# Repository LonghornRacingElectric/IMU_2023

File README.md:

# IMU Board
### ver. 2023
The hardware board containing the inertial measurement unit (IMU)

## Purpose
This board logs 6-axis accelerometer and gyroscope data and sends that data across the attached CAN bus.

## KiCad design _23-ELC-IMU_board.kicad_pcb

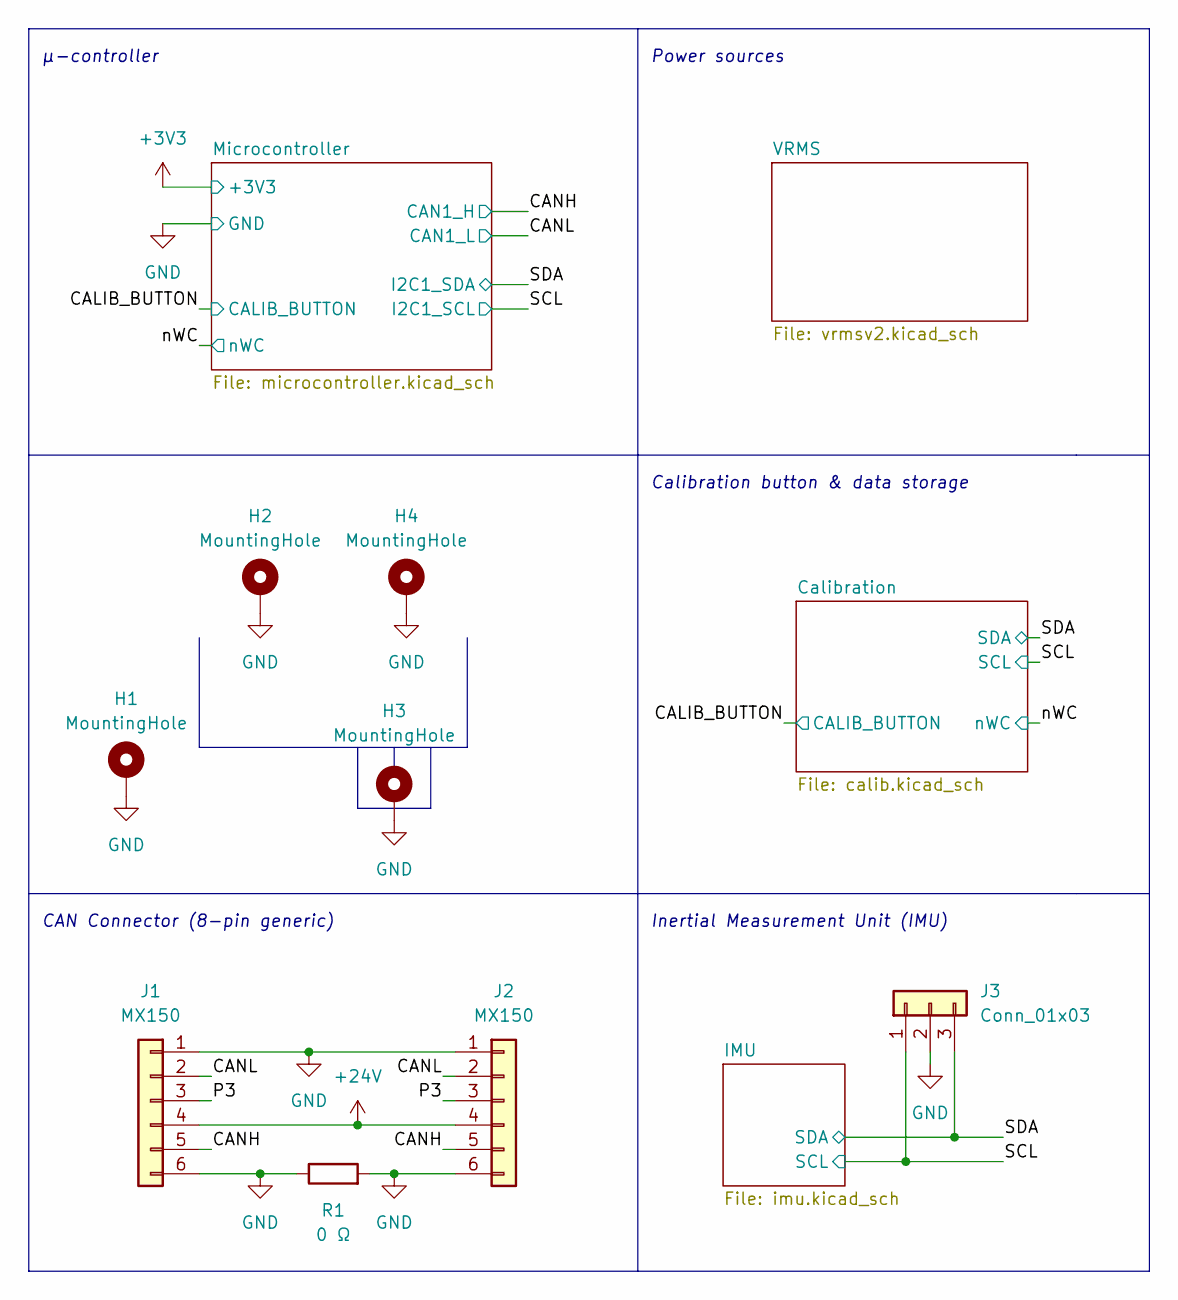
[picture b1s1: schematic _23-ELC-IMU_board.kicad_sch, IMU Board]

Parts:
H1, H2, H3, H4: MountingHole; MountingHole_3.5mm_Pad
J1, J2: MX150; Molex_Micro-Fit_3.0_43045-0600_2x03_P3.00mm_Horizontal
J3: Conn_01x03; PinHeader_1x03_P1.27mm_Vertical_SMD_Pin1Left
R1: 0 Ω; R_0603_1608Metric_Pad0.98x0.95mm_HandSolder

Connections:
+24V: J1.4, J2.4; also elsewhere on the board
/CANH: J1.5, J2.5; also elsewhere on the board
/CANL: J1.2, J2.2; also elsewhere on the board
/P3: J1.3, J2.3
/SCL: J3.1; also elsewhere on the board
/SDA: J3.3; also elsewhere on the board
GND: H1.1, H2.1, H3.1, H4.1, J1.1, J1.6, J2.1, J2.6, J3.2, R1.1, R1.2; also elsewhere on the board

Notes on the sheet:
Power sources
µ-controller
Calibration button & data storage
Inertial Measurement Unit (IMU)
CAN Connector (8-pin generic)

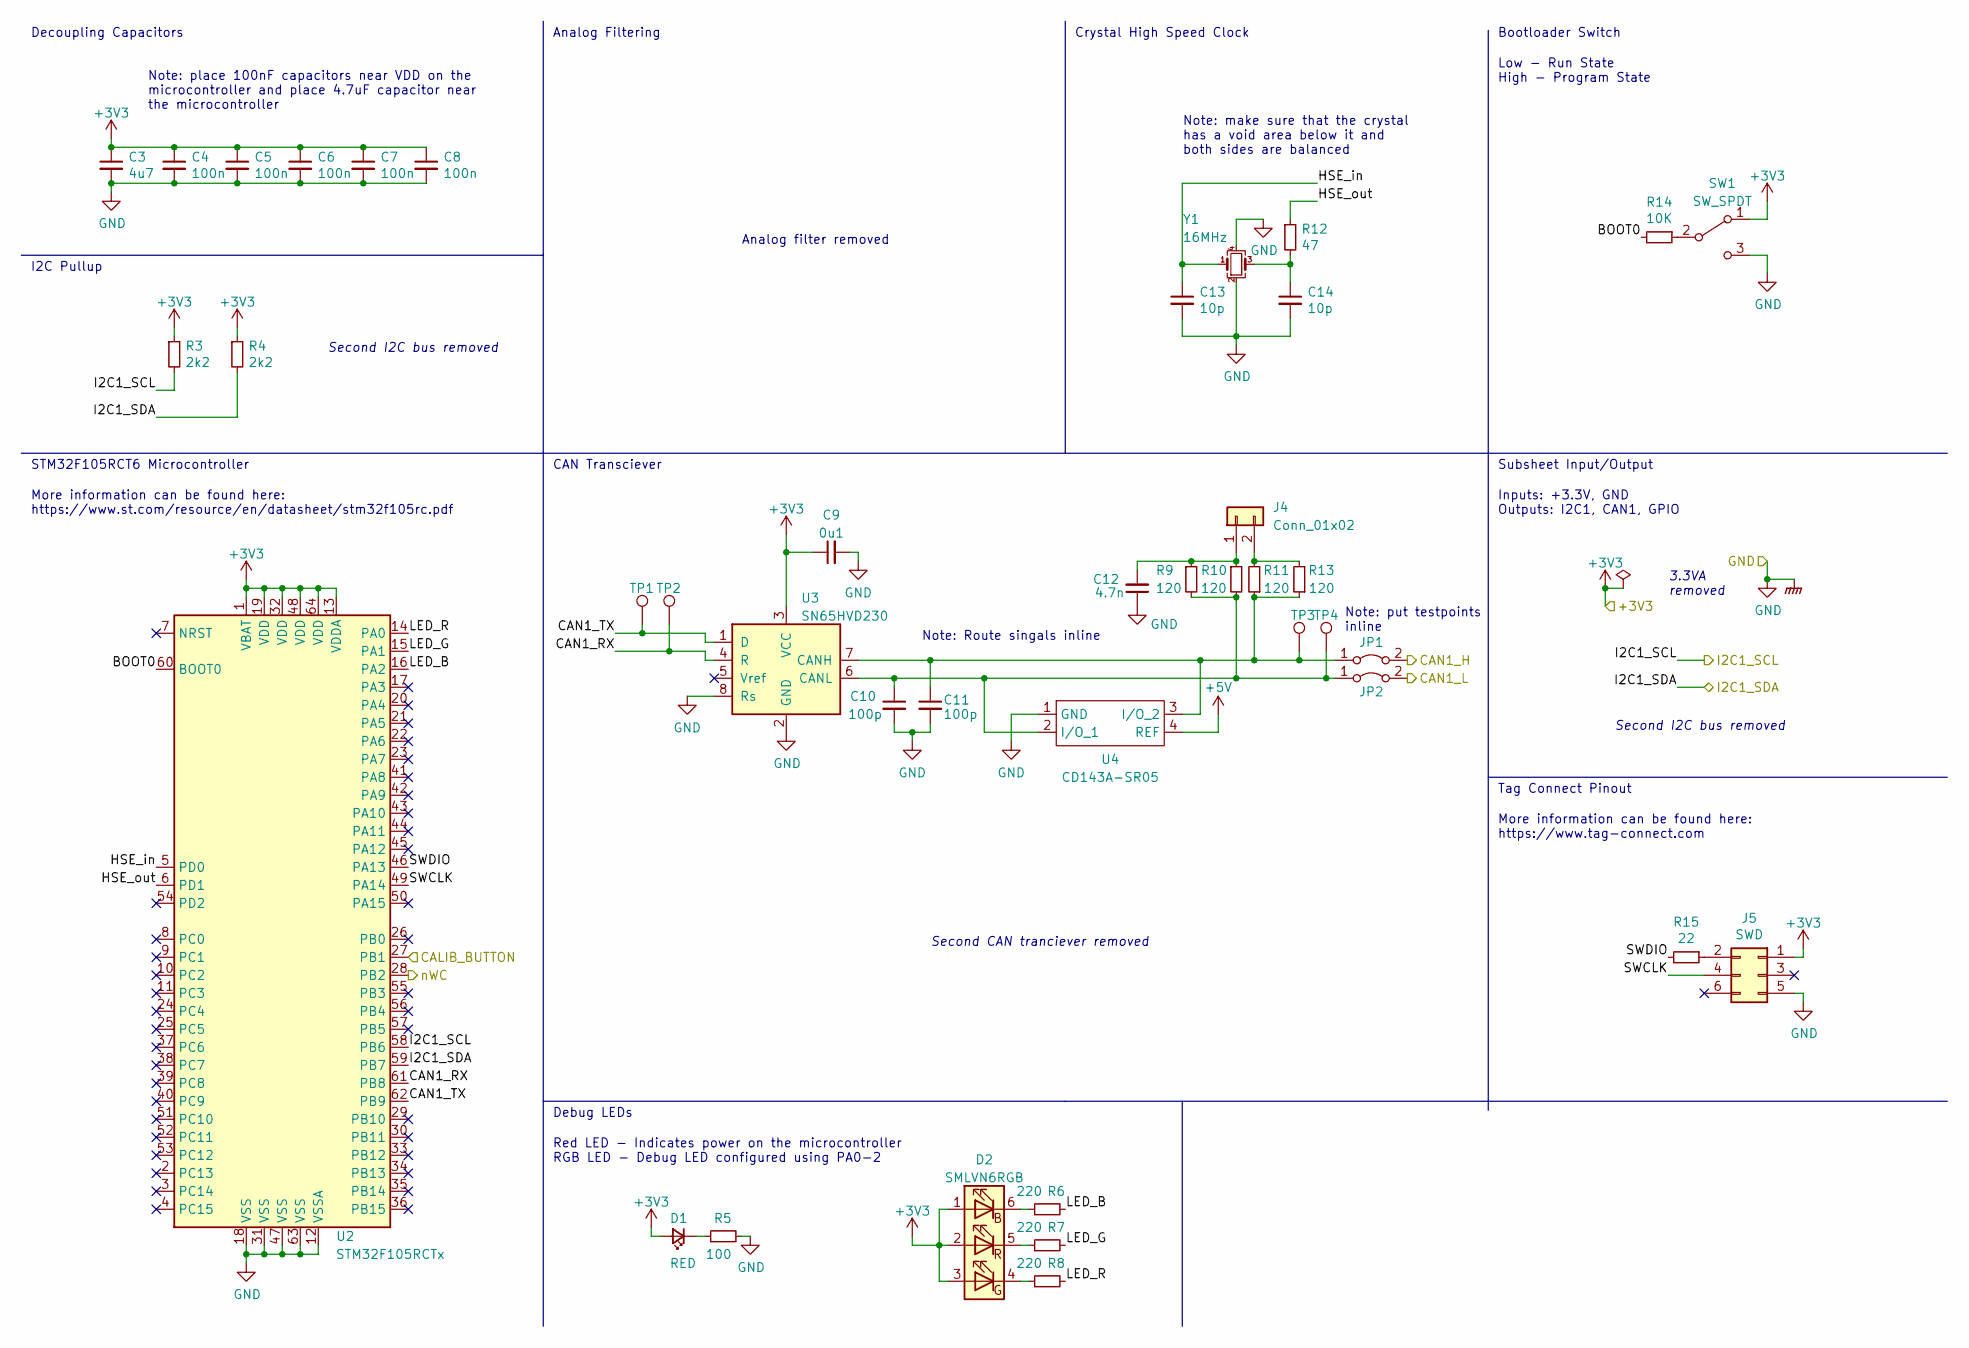
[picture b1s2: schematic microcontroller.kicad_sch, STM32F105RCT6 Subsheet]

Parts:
C3: 4u7; C_0603_1608Metric_Pad1.08x0.95mm_HandSolder
C4, C5, C6, C7, C8: 100n; C_0603_1608Metric_Pad1.08x0.95mm_HandSolder
C9: 0u1; C_0603_1608Metric_Pad1.08x0.95mm_HandSolder
C10, C11: 100p; C_0603_1608Metric_Pad1.08x0.95mm_HandSolder
C12: 4.7n; C_0603_1608Metric_Pad1.08x0.95mm_HandSolder
C13, C14: 10p; C_0603_1608Metric_Pad1.08x0.95mm_HandSolder
D1: RED; LED_0603_1608Metric_Pad1.05x0.95mm_HandSolder
D2: SMLVN6RGB; LED_ROHM_SMLVN6
J4: Conn_01x02; PinHeader_1x02_P2.54mm_Vertical
J5: SWD; PinHeader_2x03_P1.27mm_Vertical
JP1, JP2: SolderJumper-2_P1.3mm_Bridged2Bar_Pad1.0x1.5mm
R3, R4: 2k2; R_0603_1608Metric_Pad0.98x0.95mm_HandSolder
R5: 100; R_0603_1608Metric_Pad0.98x0.95mm_HandSolder
R6, R7, R8: 220; R_0603_1608Metric_Pad0.98x0.95mm_HandSolder
R9, R10, R11, R13: 120; R_0603_1608Metric_Pad0.98x0.95mm_HandSolder
R12: 47; R_0603_1608Metric_Pad0.98x0.95mm_HandSolder
R14: 10K; R_0603_1608Metric_Pad0.98x0.95mm_HandSolder
R15: 22; R_0603_1608Metric_Pad0.98x0.95mm_HandSolder
SW1: SW_SPDT; PinHeader_1x03_P1.27mm_Vertical
TP1, TP2, TP3, TP4: TestPoint_THTPad_1.0x1.0mm_Drill0.5mm
U2: STM32F105RCTx; LQFP-64_10x10mm_P0.5mm
U3: SN65HVD230; SOIC-8_3.9x4.9mm_P1.27mm
U4: CD143A-SR05; CD143ASR05
Y1: 16MHz; Crystal_SMD_3225-4Pin_3.2x2.5mm

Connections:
+3V3: C3.1, C4.1, C5.1, C6.1, C7.1, C8.1, C9.1, D1.2 (A), D2.1 (BA), D2.2 (RA), D2.3 (GA), J5.1, R3.1, R4.1, SW1.1 (A), U2.1 (VBAT), U2.13 (VDDA), U2.19 (VDD), U2.32 (VDD), U2.48 (VDD), U2.64 (VDD), U3.3 (VCC); also elsewhere on the board
+5V: U4.4 (REF); also elsewhere on the board
/CALIB_BUTTON: U2.27 (PB1); also elsewhere on the board
/CANH: JP1.2 (B); also elsewhere on the board
/CANL: JP2.2 (B); also elsewhere on the board
/Microcontroller/BOOT0: R14.2, U2.60 (BOOT0)
/Microcontroller/CAN1_RX: TP2.1, U2.61 (PB8), U3.4 (R)
/Microcontroller/CAN1_TX: TP1.1, U2.62 (PB9), U3.1 (D)
/Microcontroller/HSE_in: C13.1, U2.5 (PD0), Y1.1
/Microcontroller/HSE_out: R12.1, U2.6 (PD1)
/Microcontroller/LED_B: R6.2, U2.16 (PA2)
/Microcontroller/LED_G: R7.2, U2.15 (PA1)
/Microcontroller/LED_R: R8.2, U2.14 (PA0)
/Microcontroller/SWCLK: J5.4, U2.49 (PA14)
/Microcontroller/SWDIO: R15.2, U2.46 (PA13)
/SCL: R3.2, U2.58 (PB6); also elsewhere on the board
/SDA: R4.2, U2.59 (PB7); also elsewhere on the board
GND: C3.2, C4.2, C5.2, C6.2, C7.2, C8.2, C9.2, C10.2, C11.2, C12.1, C13.2, C14.2, J5.5, R5.2, SW1.3 (C), U2.12 (VSSA), U2.18 (VSS), U2.31 (VSS), U2.47 (VSS), U2.63 (VSS), U3.2 (GND), U3.8 (Rs), U4.1 (GND), Y1.2, Y1.4; also elsewhere on the board
unnamed: C10.1, JP2.1 (A), R9.2, R10.2, TP4.1, U3.6 (CANL), U4.2 (I/O_1)
unnamed: C11.1, JP1.1 (A), R11.1, R13.1, TP3.1, U3.7 (CANH), U4.3 (I/O_2)
unnamed: C12.2, J4.1, R9.1, R10.1
unnamed: C14.1, R12.2, Y1.3
unnamed: D1.1 (K), R5.1
unnamed: D2.4 (GK), R8.1
unnamed: D2.5 (RK), R7.1
unnamed: D2.6 (BK), R6.1
unnamed: J4.2, R11.2, R13.2
unnamed: J5.2, R15.1
unnamed: R14.1, SW1.2 (B)

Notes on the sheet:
Note: place 100nF capacitors near VDD on the microcontroller and place 4.7uF capacitor near the microcontroller
Inputs: +3.3V, GND Outputs: I2C1, CAN1, GPIO
Bootloader Switch
Low - Run State High - Program State
Note: Route singals inline
Second I2C bus removed
Analog Filtering
I2C Pullup
Tag Connect Pinout
Analog filter removed
Subsheet Input/Output
Debug LEDs
3.3VA removed
Note: make sure that the crystal has a void area below it and both sides are balanced
Decoupling Capacitors
Crystal High Speed Clock
STM32F105RCT6 Microcontroller
CAN Transciever
More information can be found here: https://www.st.com/resource/en/datasheet/stm32f105rc.pdf
More information can be found here: https://www.tag-connect.com
Note: put testpoints inline
Second CAN tranciever removed
Red LED - Indicates power on the microcontroller RGB LED - Debug LED configured using PA0-2

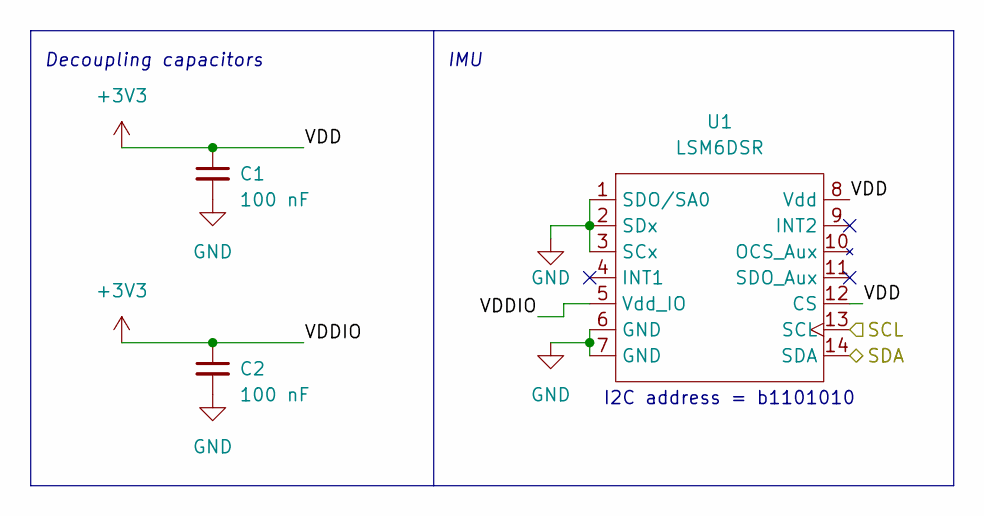
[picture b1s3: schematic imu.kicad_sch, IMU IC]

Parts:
C1, C2: 100 nF; C_0603_1608Metric_Pad1.08x0.95mm_HandSolder
U1: LSM6DSR; LGA-14L_3x2.5mm_P0.86mm

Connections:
+3V3: C1.1, C2.1, U1.5 (Vdd_IO), U1.8 (Vdd), U1.12 (CS); also elsewhere on the board
/SCL: U1.13 (SCL); also elsewhere on the board
/SDA: U1.14 (SDA); also elsewhere on the board
GND: C1.2, C2.2, U1.1 (SDO/SA0), U1.2 (SDx), U1.3 (SCx), U1.6 (GND), U1.7 (GND); also elsewhere on the board

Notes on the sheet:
IMU
Decoupling capacitors
I2C address = b1101010

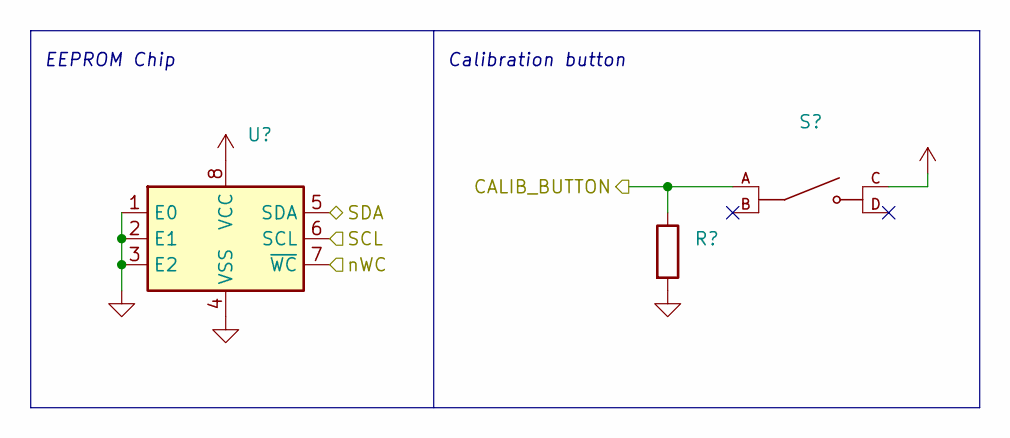
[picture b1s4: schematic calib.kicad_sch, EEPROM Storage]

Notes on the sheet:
Calibration button
EEPROM Chip

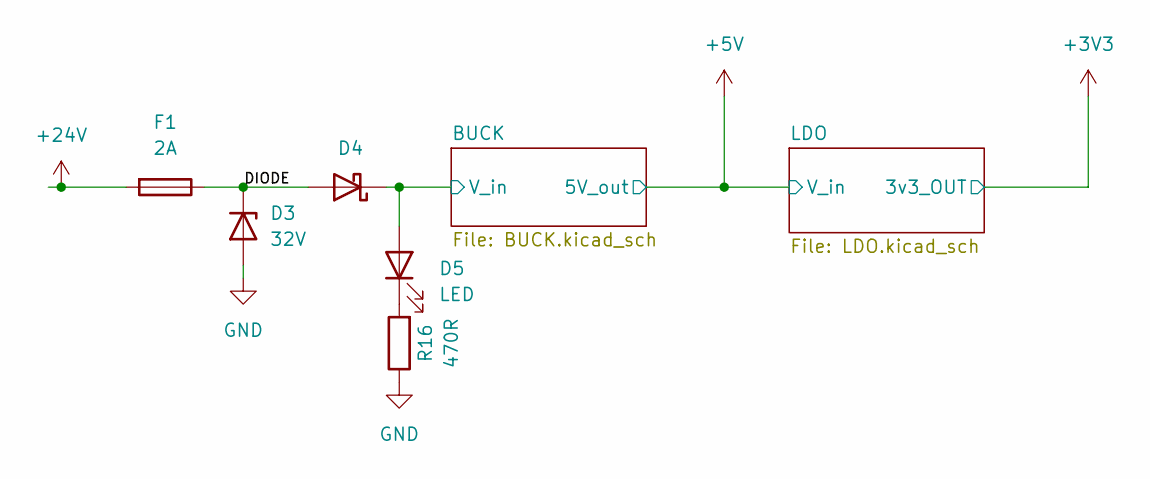
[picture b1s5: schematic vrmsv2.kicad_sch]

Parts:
D3: 32V; D_SOD-323
D4: 0.7dV; D_SMA_Handsoldering
D5: LED; LED_0603_1608Metric_Pad1.05x0.95mm_HandSolder
F1: 2A; Fuse_1206_3216Metric_Pad1.42x1.75mm_HandSolder
R16: 470R; R_0603_1608Metric_Pad0.98x0.95mm_HandSolder

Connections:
+24V: F1.2; also elsewhere on the board
/VRMS/BUCK/V_in: D4.1 (K), D5.2 (A); also elsewhere on the board
/VRMS/DIODE: D3.1 (K), D4.2 (A), F1.1
GND: D3.2 (A), R16.1; also elsewhere on the board
unnamed: D5.1 (K), R16.2

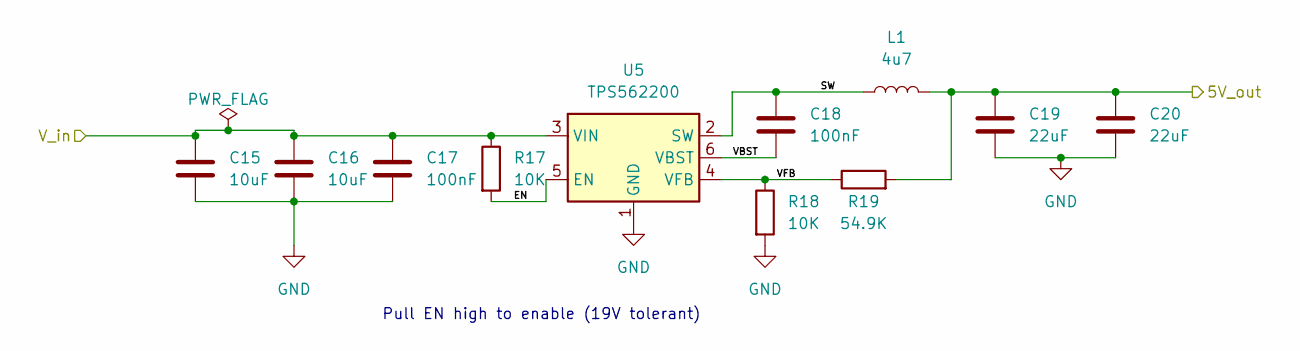
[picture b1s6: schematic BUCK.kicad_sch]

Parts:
C15, C16: 10uF; C_0603_1608Metric_Pad1.08x0.95mm_HandSolder
C17, C18: 100nF; C_0603_1608Metric_Pad1.08x0.95mm_HandSolder
C19, C20: 22uF; C_0603_1608Metric_Pad1.08x0.95mm_HandSolder
L1: 4u7; L_Sunlord_MWSA0518_5.4x5.2mm; Part # C408410
R17, R18: 10K; R_0603_1608Metric_Pad0.98x0.95mm_HandSolder
R19: 54.9K; R_0603_1608Metric_Pad0.98x0.95mm_HandSolder
U5: TPS562200; SOT-23-6

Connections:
+5V: C19.1, C20.1, L1.2, R19.2; also elsewhere on the board
/VRMS/BUCK/EN: R17.2, U5.5 (EN)
/VRMS/BUCK/SW: C18.1, L1.1, U5.2 (SW)
/VRMS/BUCK/VBST: C18.2, U5.6 (VBST)
/VRMS/BUCK/VFB: R18.1, R19.1, U5.4 (VFB)
/VRMS/BUCK/V_in: C15.1, C16.1, C17.1, R17.1, U5.3 (VIN); also elsewhere on the board
GND: C15.2, C16.2, C17.2, C19.2, C20.2, R18.2, U5.1 (GND); also elsewhere on the board

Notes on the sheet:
Pull EN high to enable (19V tolerant)

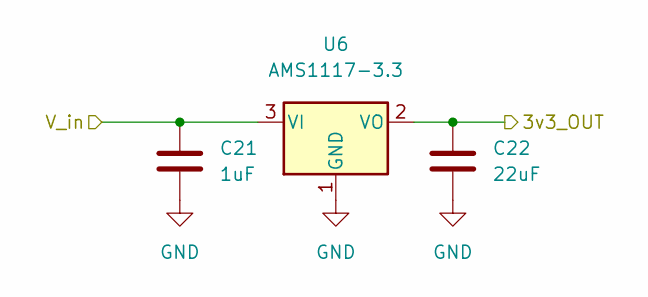
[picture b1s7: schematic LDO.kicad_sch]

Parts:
C21: 1uF; C_0603_1608Metric_Pad1.08x0.95mm_HandSolder
C22: 22uF; C_0603_1608Metric_Pad1.08x0.95mm_HandSolder
U6: AMS1117-3.3; SOT-223-3_TabPin2

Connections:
+3V3: C22.1, U6.2 (VO); also elsewhere on the board
+5V: C21.1, U6.3 (VI); also elsewhere on the board
GND: C21.2, C22.2, U6.1 (GND); also elsewhere on the board

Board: 2 copper layers, 72 parts (0 on the bottom side), 38 nets, no tracks yet.

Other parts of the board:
R2: 1 kΩ; R_0603_1608Metric_Pad0.98x0.95mm_HandSolder
S1: TS-1187A-B-A-B; SW_TS-1187A-B-A-B

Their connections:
+3V3: S1.C; also elsewhere on the board
/CALIB_BUTTON: R2.1, S1.A; also elsewhere on the board
GND: R2.2; also elsewhere on the board

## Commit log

2022-11-06 Initial commit
    Passed initial subteam review woot woot
2022-11-06 Removed backup zips
    Unnecessary after version control
2022-11-06 Minor schematic graphics change
    Just changing some things and making KiCAD create a local backup to make sure the .gitignore functions
2022-11-06 Added test points for I2C
2022-11-06 100 ohm => 1 kOhm
    Pull down probably too low
2022-11-06 Updated subsheets
2022-11-06 Adjusted CAN bus voltage to 5V
2022-11-13 Added three mounting holes
    I have no idea what to do here
2022-11-13 Pushing assorted changes
    I think I just changed a couple names
2022-11-13 Updated (?) subsheets
2022-11-15 Changed connector to 1x6
    Will be using Deutsch DT-6
2022-11-15 Added 3x1 connector for logical analyzer
    Idk how to denote a 3-pin header
2022-11-27 Removed analog filtering
    There are no analog parts in this PCB
2022-11-27 Annotated schematic
2022-11-27 Added DT connector footprints and began layout
2022-11-28 Created preliminary placement
    I hate this
2022-11-28 Good enough
    Will make a ground plane next time
2022-11-29 PCB adjustments
2022-11-29 Moved the mounting holes
2022-12-04 Redo of placement
    Really like this attempt
2022-12-04 Started drawing like 496130 areas
2022-12-04 All pours done
2022-12-05 I am happy with this layout
2022-12-05 Added 0 Ohm resistor between shield (grounded)
2022-12-05 Connected final things for this iteration of the board
2022-12-16 Added 0 Ω resistor to shield, grounded it, reannotated schematic, reassigned some footprints
    Starting layout
2022-12-16 Molex connectors wooo
2023-01-10 Added EEPROM chip for storing calibration data
    Time to redo layout
